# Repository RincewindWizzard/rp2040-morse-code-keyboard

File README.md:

# RP2040 Morse Code Keyboard

This project contains all necessary files to build your own morse button to USB keyboard.

## Preface

A long time ago I found this beautiful morse key on a local flee market.

As I am a licensed HAM operator I thought about getting into CW low power operation.
But i don't know morse code an I live in a space where operating antennas outside of my apartment is just not feasible.
So it went down to the basement for a several years.

It is currently winter here in northern germany adn weather is like shit,
so I thought about doing some nice diy projects to entertain myself.

Years ago I did a lot of arduino (atmega328p, attiny,
etc.) [projects](https://github.com/RincewindWizzard/magic-switchboard/tree/master).
Recently I stumbled across the
new [RP2040 Raspberry Pico boards](https://www.waveshare.com/wiki/RP2040-Zero#Specification).
They have an interesting new Feature: USB HID Modes.
This chip can emulate an usb keyboard to the host system, which gives you vast possibilities in the world of custom
joysticks.

This project is one of those: A USB keyboard where you have to input morse code to enter your chars.

## Build Software

The software part is build using  [platformio](https://platformio.org/).
See their [installation guide](https://docs.platformio.org/en/latest/core/installation/index.html).
There is also a good [jetbrains plugin](https://www.jetbrains.com/help/clion/platformio.html) for CLion.
If your Rp2040 is connected you just run:

    pio run -t upload -e pico

to build and upload this code.

## Build PCB

Schematics, PCB layout and 3d models will be found in the [CAD](./CAD/) folder once they are ready.

There is already a Fusion 360 [3D model of the key](./CAD/morse_key.f3d),
a [STEP File](./CAD/morse_key.step)
and a [drawing of the drill hole positions](./CAD/morse_key_drilll_holes.pdf).

Here is a rendering of the pcb with the mechanical key and the rp2040 zero mounted on.

The pin headers are for further debugging and modification.

The [STEP file for rp2040 zero](https://grabcad.com/library/rp2040-zero-2) is from grabcad.com.

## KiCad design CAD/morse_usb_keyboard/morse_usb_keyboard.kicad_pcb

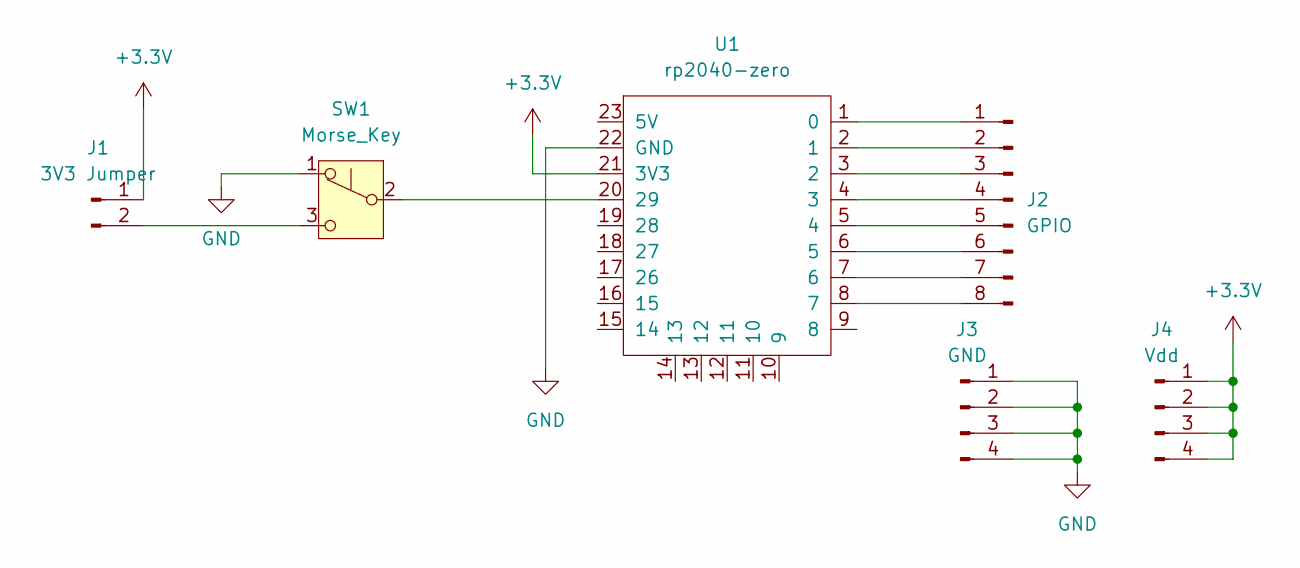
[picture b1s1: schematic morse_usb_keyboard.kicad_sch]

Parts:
J1: 3V3 Jumper; PinSocket_1x02_P2.54mm_Vertical
J2: GPIO; PinSocket_1x08_P2.54mm_Vertical
J3: GND; PinSocket_1x04_P2.54mm_Vertical
J4: Vdd; PinSocket_1x04_P2.54mm_Vertical
SW1: Morse_Key; mose_key_button
U1: rp2040-zero; rp2040-zero-tht

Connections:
+3.3V: J1.1, J4.1, J4.2, J4.3, J4.4, U1.21 (3V3)
GND: J3.1, J3.2, J3.3, J3.4, SW1.1 (A), U1.22 (GND)
unnamed: J1.2, SW1.3 (C)
unnamed: J2.1, U1.1 (0)
unnamed: J2.2, U1.2 (1)
unnamed: J2.3, U1.3 (2)
unnamed: J2.4, U1.4 (3)
unnamed: J2.5, U1.5 (4)
unnamed: J2.6, U1.6 (5)
unnamed: J2.7, U1.7 (6)
unnamed: J2.8, U1.8 (7)
unnamed: SW1.2 (B), U1.20 (29)

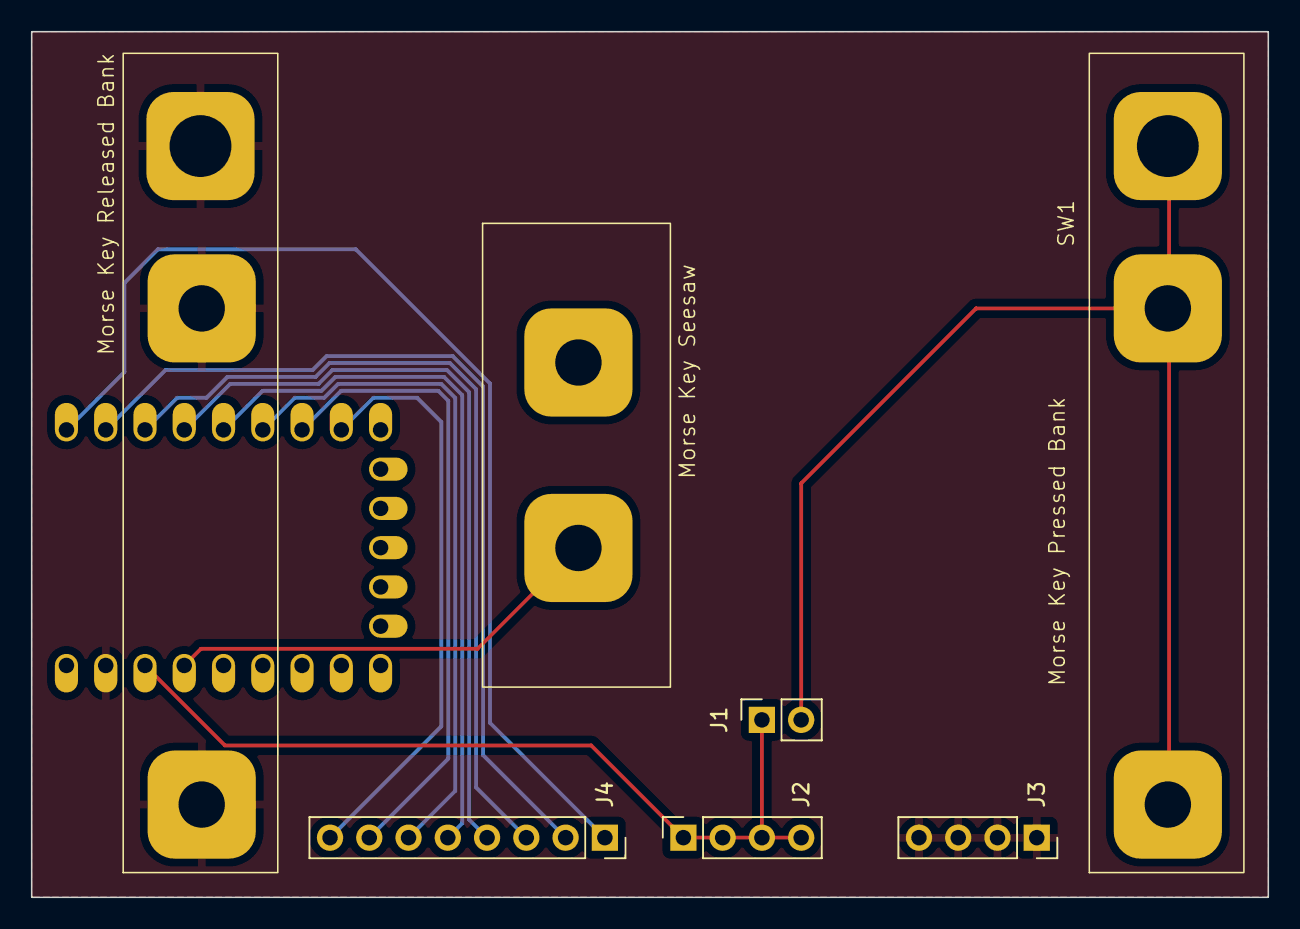
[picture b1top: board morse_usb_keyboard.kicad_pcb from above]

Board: 2 copper layers, 80.0 x 56.0 mm, 6 parts (0 on the bottom side), 12 nets.

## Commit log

2024-02-09 init
2024-02-09 laggy debouncer
2024-02-09 morse code keying geht
2024-02-11 CircuitPython base template
2024-02-11 debug class
2024-02-11 Working Keyboard
2024-02-11 aufräumen
2024-02-11 morse decoder struktur
2024-02-11 NIce
2024-02-11 first working parsser
2024-02-11 it works, bitches!
2024-02-11 it works as USB HID
2024-02-11 querty and fail led
2024-02-17 Readme
2024-02-17 3d models
2024-02-17 PCB with 3d
2024-02-17 Gerber and drill files
2024-02-17 In Produktion gegeben
